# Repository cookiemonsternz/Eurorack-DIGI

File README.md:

# DIGI

_FPGA based programmable eurorack effects module_

#### What?
Yet another in my line of eurorack modules. This module is a prototyping platform for fpga based effects. It has a basic mono audio codec, two rotary encoders and 3 switches. It has two small led based displays in order to provide some feedback for the encoders. It consists of two user programmable leds with a diffuser.

DIGI utilises an ice40UP5K fpga chip, featuring 5280 luts and a 48Mhz clock. This is accompanied by a USB-SPI interface for easy programming. The board includes 64Mbits of PSRAM via single channel SPI and 256kbits of flash EEPROM. 

#### Why?
First and foremost: FPGAs are cool. Unfortunately, the world is quite starved of easy to use FPGA devboards, and especially so one which is designed for audio. This module acts as an easy to use prototyping environment for audio processing which would not be possible on MCUs.

This does kind of act as a counterpart to REV, but with an FPGA as to an MCU. This provides a bit more flexibility (and performance) and also provides a lot more memory to play with. 

#### How to use?
The board has a simple audio input and output, as well as two rotary encoders and switches, which are user programmable.

In terms of getting it set up, you'll need to program the fpga. To do this, follow the general setup guides for lattice radiant. It should be configured as a project for the iCE40UP5K-SG48I. An example showing the board acting as a basic buffer is available in the gateware folder.

Once assembled, the board uses a standard eurorack connector as well as standard 3.5mm audio jacks for input and output. Pretty plug and play :)

## Renders

## Schematics
Schematics are available as a [pdf](./hardware/digi/plots/digi.pdf) or as svgs in [hardware/digi/plots](./hardware/digi/plots/).

## Zine Page

## BOM
_Needed is how many I personally need :)_
| Part                            | Quantity | Needed | Source     | Link                                                                                                                                                           | Lot / Min Amount | Unit    | Net     | Running |
|---------------------------------|----------|--------|------------|----------------------------------------------------------------------------------------------------------------------------------------------------------------|------------------|---------|---------|---------|
| **Capacitors**                      |          |        |            |                                                                                                                                                                |                  |         |         |         |
| 20p Cap, 0402                   | 2        | 2      | JLCPCB     | https://jlcpcb.com/partdetail/1906-0402CG200J500NT/C1554                                                                                                       | 1                | $0.0021 | $0.0042 | $0.01   |
| 10n Cap, 0402                   | 4        | 4      | JLCPCB     | https://jlcpcb.com/partdetail/15869-CL05B103KB5NNNC/C15195                                                                                                     | 1                | $0.0025 | $0.0100 | $0.01   |
| 100n Cap, 0402                  | 25       | 25     | JLCPCB     | https://jlcpcb.com/partdetail/291005-CL05B104KB54PNC/C307331                                                                                                   | 1                | $0.0076 | $0.1900 | $0.20   |
| 1u Cap, 0402                    | 12       | 12     | JLCPCB     | https://jlcpcb.com/partdetail/53938-CL05A105KA5NQNC/C52923                                                                                                     | 1                | $0.0069 | $0.0828 | $0.28   |
| 4.7u Cap, 0402                  | 6        | 6      | JLCPCB     | https://jlcpcb.com/partdetail/24469-CL05A475MP5NRNC/C23733                                                                                                     | 1                | $0.0107 | $0.0642 | $0.35   |
| 10u Cap, 0402                   | 2        | 2      | JLCPCB     | https://jlcpcb.com/partdetail/16204-CL05A106MQ5NUNC/C15525                                                                                                     | 1                | $0.0186 | $0.0372 | $0.38   |
| 22u Cap, 0603                   | 1        | 1      | JLCPCB     | https://jlcpcb.com/partdetail/60514-CL10A226MQ8NRNC/C59461                                                                                                     | 1                | $0.0224 | $0.0224 | $0.41   |
| 10u Electrolytic Cap, P1.5xD4.0 | 2        | 0      | LCSC       | https://www.lcsc.com/product-detail/C503219.html                                                                                                               | 10               | $0.0143 | $0.0000 | $0.41   |
| 47u Electrolytic Cap, P2.5xD6.3 | 5        | 0      | LCSC       | https://www.lcsc.com/product-detail/C107641.html?spm=wm.fly.bg.7.xh___wm.fly.tp.1.ml&lcsc_vid=QAJaU1UHTldXXgADFFBaVFVfFFAMBl0CFVAIBQZQRVMxVlNeRlNcV1JXRFRaXjtW | 10               | $0.0665 | $0.0000 | $0.41   |
| 470u Electrolytic Cap, P5xD10.0 | 2        | 0      | LCSC       | https://www.lcsc.com/product-detail/C338196.html?spm=wm.fly.bg.3.xh___wm.fly.tp.1.ml&lcsc_vid=QAJaU1UHTldXXgADFFBaVFVfFFAMBl0CFVAIBQZQRVMxVlNeRlNcV1JXRFRaXjtW | 5                | $0.1883 | $0.0000 | $0.41   |
| **Resistors**                       |          |        |            |                                                                                                                                                                |                  |         |         |         |
| 0? Resistor, 0402               | 6        | 6      | JLCPCB     | https://jlcpcb.com/partdetail/17853-0402WGF0000TCE/C17168                                                                                                      | 1                | $0.001  | $0.0066 | $0.41   |
| 10? Resistor, 0402              | 1        | 1      | JLCPCB     | https://jlcpcb.com/partdetail/25820-0402WGF100JTCE/C25077                                                                                                      | 1                | $0.001  | $0.0009 | $0.41   |
| 100? Resistor, 0402             | 4        | 4      | JLCPCB     | https://jlcpcb.com/partdetail/25819-0402WGF1000TCE/C25076                                                                                                      | 1                | $0.0012 | $0.0048 | $0.42   |
| 470? Resistor, 0402             | 1        | 1      | JLCPCB     | https://jlcpcb.com/partdetail/25860-0402WGF4700TCE/C25117                                                                                                      | 1                | $0.0010 | $0.0010 | $0.42   |
| 1k? Resistor, 0402              | 2        | 2      | JLCPCB     | https://jlcpcb.com/partdetail/12256-0402WGF1001TCE/C11702                                                                                                      | 1                | $0.0011 | $0.0022 | $0.42   |
| 2.2k? Resistor, 0402            | 2        | 2      | JLCPCB     | https://jlcpcb.com/partdetail/26622-0402WGF2201TCE/C25879                                                                                                      | 1                | $0.0010 | $0.0020 | $0.42   |
| 10k? Resistor, 0805             | 8        | 8      | JLCPCB     | https://jlcpcb.com/partdetail/18102-0805W8F1002T5E/C17414                                                                                                      | 1                | $0.0034 | $0.0272 | $0.45   |
| 12k? Resistor, 0402             | 1        | 1      | JLCPCB     | https://jlcpcb.com/partdetail/26495-0402WGF1202TCE/C25752                                                                                                      | 1                | $0.0010 | $0.0010 | $0.45   |
| 39k? Resistor, 0402             | 1        | 1      | JLCPCB     | https://jlcpcb.com/partdetail/26526-0402WGF3902TCE/C25783                                                                                                      | 1                | $0.0011 | $0.0011 | $0.45   |
| 100k? Resistor, 0402            | 1        | 1      | JLCPCB     | https://jlcpcb.com/partdetail/26484-0402WGF1003TCE/C25741                                                                                                      | 1                | $0.0010 | $0.0010 | $0.45   |
| 1M? Resistor, 0402              | 1        | 1      | JLCPCB     | https://jlcpcb.com/partdetail/26826-0402WGF1004TCE/C26083                                                                                                      | 1                | $0.0011 | $0.0011 | $0.46   |
| **Diodes**                          |          |        |            |                                                                                                                                                                |                  |         |         |         |
| 1N4148WS, SOD-323               | 1        | 1      | JLCPCB     | https://jlcpcb.com/partdetail/2485-1N4148WS/C2128                                                                                                              | 1                | $0.0092 | $0.0092 | $0.46   |
| 1N5819WS, SOD-323               | 4        | 4      | JLCPCB     | https://jlcpcb.com/partdetail/GuangdongHottech-1N5819WS/C191023                                                                                                | 1                | $0.0111 | $0.0444 | $0.51   |
| **Other Components**                |          |        |            |                                                                                                                                                                |                  |         |         |         |
| TL072CDT                        | 1        | 1      | JLCPCB     | https://jlcpcb.com/partdetail/STMicroelectronics-TL072CDT/C6961                                                                                                | 1                | $0.1570 | $0.1570 | $0.67   |
| EC11 Rotary Encoder SW          | 2        | 0      | Aliexpress | https://www.aliexpress.com/item/1005010400760178.html                                                                                                          | 5                | $0.8580 | $0.0000 | $0.67   |
| SPDT Switch                     | 3        | 3      | Aliexpress | https://www.aliexpress.com/item/1005005370002265.html                                                                                                          | 5                | $0.8520 | $4.2600 | $4.93   |
| PJ301M-12 Audio Jack            | 2        | 0      | Aliexpress | https://www.aliexpress.com/item/1005004864182675.html                                                                                                          | 10               | $0.4440 | $0.0000 | $4.93   |
| 2x08 IDC Connector              | 1        | 0      | LCSC       | https://www.lcsc.com/product-detail/C7430313.html                                                                                                              | 5                | $0.0993 | $0.0000 | $4.93   |
| X322512MSB4SI 12MHz Crystal     | 1        | 1      | JLCPCB     | https://jlcpcb.com/partdetail/YXC_CrystalOscillators-X322512MSB4SI/C9002                                                                                       | 1                | $0.0740 | $0.0740 | $5.00   |
| USB B Micro Port                | 1        | 1      | JLCPCB     | https://jlcpcb.com/partdetail/SHOUHAN-MicroXNJ/C404969                                                                                                         | 1                | $0.0406 | $0.0406 | $5.04   |
| 256kB EEPROM, AT24C256C-SSHL-T  | 1        | 1      | JLCPCB     | https://jlcpcb.com/partdetail/MicrochipTech-AT24C256C_SSHLT/C6482                                                                                              | 1                | $0.3886 | $0.3886 | $5.43   |
| 64Mbit PSRAM, APS6404L-SQN-SN   | 1        | 1      | JLCPCB     | https://jlcpcb.com/partdetail/APMemory-APS6404L_SQNSN/C5360304                                                                                                 | 1                | $2.4684 | $2.4684 | $7.90   |
| Neopixel tht, 5mm               | 8        | 8      | Aliexpress | https://www.aliexpress.com/item/1005006447915276.html                                                                                                          | 20               | $0.2595 | $5.1900 | $13.09  |
| Audio Codec, ES8311             | 1        | 1      | JLCPCB     | https://jlcpcb.com/partdetail/1044199-ES8311/C962342                                                                                                           | 1                | $0.5514 | $0.5514 | $13.64  |
| Reset Button                    | 1        | 1      | JLCPCB     | https://jlcpcb.com/partdetail/XUNPU-TS_1088AR02016/C720477                                                                                                     | 1                | $0.0551 | $0.0551 | $13.69  |
| Ferrite Bead, 600R              | 2        | 2      | JLCPCB     | https://jlcpcb.com/partdetail/Sunlord-GZ2012D601TF/C1017                                                                                                       | 1                | $0.0323 | $0.0646 | $13.76  |
| 22uH Inductor, 0805             | 2        | 2      | JLCPCB     | https://jlcpcb.com/partdetail/Sunlord-SDFL2012T220KTF/C32375                                                                                                   | 1                | $0.0689 | $0.1378 | $13.90  |
| LED Yellow                      | 1        | 1      | JLCPCB     | https://jlcpcb.com/partdetail/Hubei_KENTOElec-KT0805Y/C2296                                                                                                    | 1                | $0.0152 | $0.0152 | $13.91  |
| LED Green                       | 1        | 1      | JLCPCB     | https://jlcpcb.com/partdetail/Hubei_KENTOElec-KT0805G/C2297                                                                                                    | 1                | $0.0162 | $0.0162 | $13.93  |
| LED Red                         | 1        | 1      | JLCPCB     | https://jlcpcb.com/partdetail/85425-NCD0805R1/C84256                                                                                                           | 1                | $0.0133 | $0.0133 | $13.94  |
| AMS1117-3.3                     | 1        | 1      | JLCPCB     | https://jlcpcb.com/partdetail/Advanced_MonolithicSystems-AMS1117_33/C6186                                                                                      | 1                | $0.1971 | $0.1971 | $14.14  |
| XL1509-ADJ                      | 2        | 2      | JLCPCB     | https://jlcpcb.com/partdetail/XLSEMI-XL1509ADJE1/C74192                                                                                                        | 1                | $0.2717 | $0.5434 | $14.68  |
| **Other**                           |          |        |            |                                                                                                                                                                |                  |         |         |         |
| PCB                             | 1        | 1      | JLCPCB     | NA                                                                                                                                                             | 5                | $1.6600 | $8.3000 | $22.98  |
| Aluminium Plate (100x200x2mm)   | 1        | 1      | Aliexpress | https://www.aliexpress.com/item/1005007160296738.html                                                                                                          | 1                | $6.2300 | $6.2300 | $29.21  |
| **Total**                           |          |        |            |                                                                                                                                                                |                  |         |         | $29.21  |

| **Totals**                          | **Money**  |
|---------------------------------|--------|
| Aliexpress, Inc. Shipping + Tax | $24.57 |
| JLCPCB, Inc. Shipping + Tax     | $38.84 |
| Total                           | $63.41 |

## CAD Links
Heres the links to the CAD source, Onshape:
[Panel source](https://cad.onshape.com/documents/423b155ae421053f9c0db9a4/w/13826012c5a1515169c92444/e/776c4f51f2d171959c208a60?renderMode=0&uiState=6a7d7e6ffb2cc2f8f4025e10)

## Directory Structure
- **hardware/**
    - **bom/** - BOM Files (CSV and LibreOffice Calc)
    - **cad/** - CAD Files
        - **render/** - Files for rendering (inc. gltf models)
    - **digi/** - KiCad files
        - **lib/** - External libraries
        - **production/** - Production files (Gerber, etc.)
        - **plots/** - Schematic plot
- **journals/**
- **zine/** - Zine page

#### This project was created for [Hack Club](https://hackclub.com/) - [Fallout](https://fallout.hackclub.com/)

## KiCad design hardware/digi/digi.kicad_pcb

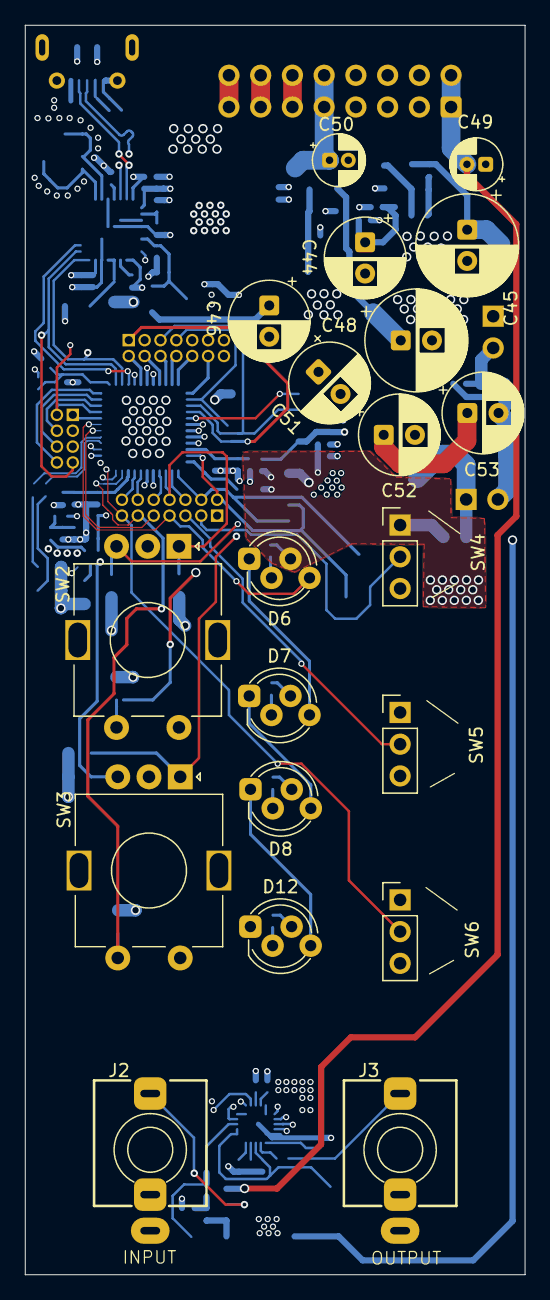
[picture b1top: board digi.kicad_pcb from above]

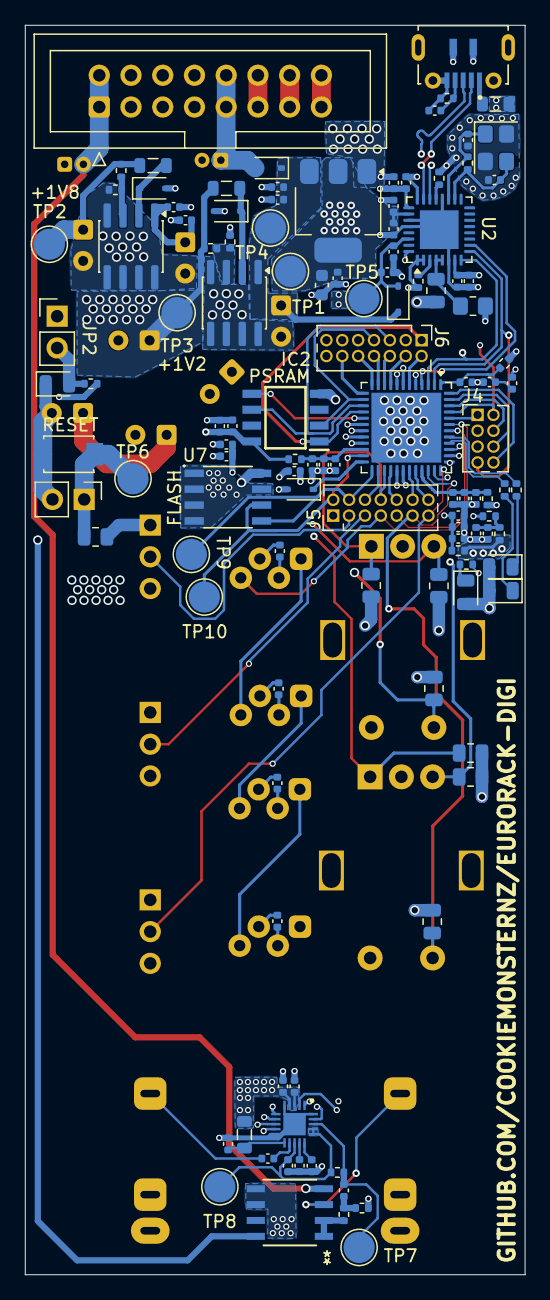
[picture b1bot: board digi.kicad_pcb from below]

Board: 6 copper layers, 40.0 x 100.0 mm, 139 parts (119 on the bottom side), 86 nets.

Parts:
C1, C4, C6, C8, C11, C14, C19, C21, C23, C25, C30, C31, C34, C36, C37, C38, C39, C42, C54, C55, C60: 100n; C_0402_1005Metric
C2, C40: 10u; C_0402_1005Metric
C3, C7, C10, C13, C26, C27, C28, C29, C32, C33, C43, C47: 1u; C_0402_1005Metric
C5, C9, C12, C15: 10n; C_0402_1005Metric
C16, C17: 20p; C_0402_1005Metric
C18, C20, C22, C24, C35, C61: 4.7u; C_0402_1005Metric
C41: 22u; C_0603_1608Metric
C44, C46, C51, C52, C53: 47u; CP_Radial_D6.3mm_P2.50mm
C45, C48: 470u; CP_Radial_D8.0mm_P2.50mm
C49, C50: 10u; CP_Radial_D4.0mm_P1.50mm
D1: 1N4148; D_SOD-323
D2: LED; LED_0805_2012Metric
D3, D4, D5, D17: 1N5819; D_SOD-323
D6, D7, D8, D12: NeoPixel_THT; LED_D5.0mm-4_RGB_Staggered_Pins
D9: LED_R; LED_0805_2012Metric
D10: LED_G; LED_0805_2012Metric
D11: LED_B; LED_0805_2012Metric
IC1: ES8311; QFN40P300X300X60-21N
IC2: APS6404L-SQN-SN; SOIC127P600X175-8N
J1: USB_B_Micro; SHOUHAN_MICROXNJ
J2: IN; Jack_3.5mm_QingPu_WQP-PJ301M-12_Vertical
J3: OUT; Jack_3.5mm_QingPu_WQP-PJ301M-12_Vertical
J4: Bank 2; PinHeader_2x04_P1.27mm_Vertical
J5: Bank 0; PinHeader_2x07_P1.27mm_Vertical
J6: Bank 1; PinHeader_2x07_P1.27mm_Vertical
J10: Conn_02x08_Odd_Even; IDC-Header_2x08_P2.54mm_Vertical
JP1: RESET_J; PinHeader_1x02_P2.54mm_Vertical
JP2: DONE_J; PinHeader_1x02_P2.54mm_Vertical
L1: 600R/1A; L_0805_2012Metric
L2: 180r-100M; L_0805_2012Metric
L3, L4: 47uH; L_0805_2012Metric
R1, R28, R29, R30: 100; R_0402_1005Metric
R2, R3, R4, R5, R6, R23: 0; R_0402_1005Metric
R7, R15, R16, R17, R18, R19, R20, R21: 10k; R_0805_2012Metric
R8, R22: 2.2k; R_0402_1005Metric
R9, R13: 1M; R_0402_1005Metric
R10: 12k; R_0402_1005Metric
R11: 100k; R_0402_1005Metric
R12: 39k; R_0402_1005Metric
R14: DNP; R_0805_2012Metric_Pad1.20x1.40mm_HandSolder
R24: 470; R_0402_1005Metric
R25, R26: 1k; R_0402_1005Metric
R27: 10; R_0402_1005Metric
SW1: RESET_SW; SW_TS-1088-AR02016
SW2: Encoder1; RotaryEncoder_Alps_EC11E-Switch_Vertical_H20mm_MountingHoles
SW3: Encoder2; RotaryEncoder_Alps_EC11E-Switch_Vertical_H20mm_MountingHoles
SW4, SW5, SW6: SW_SPDT; PinHeader_1x03_P2.54mm_Vertical
TP1: 3V3; TestPoint_Pad_D2.5mm
TP2: 1V8; TestPoint_Pad_D2.5mm
TP3: 1V2; TestPoint_Pad_D2.5mm
TP4: VDD; TestPoint_Pad_D2.5mm
TP5: VBUS; TestPoint_Pad_D2.5mm
TP6: RESET; TestPoint_Pad_D2.5mm
TP7: AUDIO_IN; TestPoint_Pad_D2.5mm
TP8: AUDIO_VMID; TestPoint_Pad_D2.5mm
TP9: FLASH_SDA; TestPoint_Pad_D2.5mm
TP10: FLASH_CLK; TestPoint_Pad_D2.5mm
U1: ICE40UP5K-SG48ITR; QFN-48-1EP_7x7mm_P0.5mm_EP5.6x5.6mm
U2: FT4222HQ; VQFN-32-1EP_5x5mm_P0.5mm_EP3.1x3.1mm
U3: TL072; D8_TEX_STM
U4: AMS1117-3.3; SOT-223-3_TabPin2
U5, U6: XL1509-ADJ; SOIC-8_3.9x4.9mm_P1.27mm
U7: AT24C256C-SSHL-T; SOIC127P600X175-8N
Y1: 12MHz - X322512MSB4SI; Crystal_SMD_3225-4Pin_3.2x2.5mm

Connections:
+1V2: C48.1, L4.2, R2.1, R3.1, R27.2, TP3.1 (1_1)
+1V8: C34.1, C35.1, C45.1, IC2.8 (VDD), L3.2, R5.1, R24.2, TP2.1 (1_1)
+3V3: C6.1, C20.1, C21.1, C22.1, C23.1, C24.1, C25.1, C30.1, C31.1, C37.1, C38.1, C41.1, C42.1, C54.1, C55.1, C60.1, C61.1, D1.2 (A), D6.3 (VDD), D7.3 (VDD), D8.3 (VDD), D9.2 (A), D10.2 (A), D11.2 (A), D12.3 (VDD), IC1.3 (PVDD), IC1.4 (DVDD), L2.1, R4.1, R6.1, R7.1, R8.1, R15.1, R16.1, R17.1, R18.1, R19.1, R20.1, R21.2, R22.2, SW4.1 (A), SW5.1 (A), SW6.1 (A), TP1.1 (1_1), U2.1 (DEBUGGER), U2.2 (~STEST_RST), U2.7 (VCCIO), U2.25 (VOUT3V3), U2.26 (VCCIN), U4.2 (VO), U7.8 (VCC)
+12V: C50.1, D17.2 (A), J10.9, J10.10, U3.8 (V+)
-12V: C49.2, J10.1, J10.2, U3.4 (V-)
/SPI_VCCIO1: C10.1, C11.1, C12.1, R5.2, U1.22 (SPI_VCCIO1)
/USB_D+: J1.3 (D+), U2.22 (DM)
/USB_D-: J1.2 (D-), U2.23 (DP)
/VCCIO_0: C13.1, C14.1, C15.1, R6.2, U1.33 (VCCIO_0)
/VCCIO_2: C7.1, C8.1, C9.1, R4.2, U1.1 (VCCIO_2)
AUDIO_VMID: C26.1, IC1.13 (OUTN), IC1.16 (VMID), IC1.17 (MIC1N), R13.2, TP8.1 (1_1)
AVDD: C29.1, IC1.11 (AVDD), L2.2
CDONE: JP2.1 (A), U1.7 (CDONE)
CRESET: JP1.1 (A), R7.2, SW1.1, TP6.1 (1_1), U1.8 (~CRESET)
ENCODER_1_A: J5.8, R17.2, SW2.A, U1.27 (IOT_38b)
ENCODER_1_B: J5.6, R18.2, SW2.B, U1.26 (IOT_39a)
ENCODER_1_SW: J5.14, R15.2, SW2.S1, U1.32 (IOT_43a)
ENCODER_2_A: J5.10, R19.2, SW3.A, U1.28 (IOT_41a)
ENCODER_2_B: J5.12, R20.2, SW3.B, U1.31 (IOT_42b)
ENCODER_2_SW: J5.11, R16.2, SW3.S1, U1.34 (IOT_44b)
GND: C1.2, C2.2, C3.2, C4.2, C5.2, C6.2, C7.2, C8.2, C9.2, C10.2, C11.2, C12.2, C13.2, C14.2, C15.2, C16.2, C17.2, C18.2, C19.2, C20.2, C21.2, C22.2, C23.2, C24.2, C25.2, C26.2, C27.2, C28.2, C29.2, C30.2, C31.2, C34.2, C35.2, C36.2, C37.2, C38.2, C39.2, C40.2, C41.2, C42.2, C43.2, C44.2, C45.2, C46.2, C47.2, C48.2, C49.1, C50.2, C51.2, C52.2, C53.2, C54.2, C55.2, C60.2, C61.2, D2.1 (K), D4.2 (A), D5.2 (A), D6.2 (GND), D7.2 (GND), D8.2 (GND), D12.2 (GND), IC1.5 (DGND), IC1.10 (AGND), IC1.20 (CE), IC1.21 (EP), IC2.4 (VSS), J1.5 (GND), J1.SH (Shield), J2.S, J2.TN, J3.S, J3.TN, J10.3, J10.4, J10.5, J10.6, J10.7, J10.8, JP1.2 (B), R10.2, R12.1, R14.1, R23.2, R25.1, R26.1, SW1.2, SW2.C, SW2.S2, SW3.C, SW3.S2, SW4.3 (C), SW5.3 (C), SW6.3 (C), U1.49 (GND), U2.6 (DGND), U2.20 (UGND), U2.24 (UGND), U2.27 (AGND), U2.28 (DGND), U2.33 (EP), U3.5 (+), U3.6 (-), U4.1 (GND), U5.4 (~EN), U5.5 (GND), U5.6 (GND), U5.7 (GND), U5.8 (GND), U6.4 (~EN), U6.5 (GND), U6.6 (GND), U6.7 (GND), U6.8 (GND), U7.1 (A0), U7.2 (A1), U7.3 (A2), U7.4 (GND), U7.7 (WP), Y1.2 (G), Y1.4 (G)
ICE_I2C_CLK: IC1.1 (CCLK), J5.2, TP10.1 (1_1), U1.23 (IOT_37a), U7.6 (SCL)
ICE_I2C_SDA: IC1.19 (CDATA), J5.4, TP9.1 (1_1), U1.25 (IOT_36b), U7.5 (SDA)
ICE_I2S_BCLK: IC1.6 (SCLK/DMIC_SCL), J4.6, U1.47 (IOB_2a)
ICE_I2S_DIN: IC1.9 (DSDIN), J4.8, U1.48 (IOB_4a)
ICE_I2S_DOUT: IC1.7 (ASDOUT), J4.1, U1.44 (IOB_3b_G6)
ICE_I2S_MCLK: IC1.2 (MCLK), J4.4, U1.46 (IOB_0a)
ICE_I2S_WS: IC1.8 (LRCK), J5.1, U1.38 (IOT_50b)
ICE_LED_0: R30.1, U1.39 (RGB0)
ICE_LED_1: R29.1, U1.40 (RGB1)
ICE_LED_2: R28.1, U1.41 (RGB2)
ICE_SPI0_MISO: IC2.2 (SO/SIO[1]), J6.7, U1.14 (IOB_32a_SPI_SO)
ICE_SPI0_MOSI: IC2.5 (SI/SIO[0]), J6.3, U1.17 (IOB_33b_SPI_SI)
ICE_SPI0_SCK: IC2.6 (SCLK), J6.5, U1.15 (IOB_34a_SPI_SCK)
ICE_SPI1_MISO: J4.7, U1.2 (IOB_6a), U2.9 (MISO)
ICE_SPI1_MOSI: J4.5, U1.4 (IOB_8a), U2.10 (MOSI)
ICE_SPI1_SCK: J4.3, U1.3 (IOB_9b), U2.8 (SCK)
IOB_13b: J6.2, U1.6 (IOB_13b)
IOB_16a: J6.4, U1.9 (IOB_16a)
IOB_18a: J6.6, U1.10 (IOB_18a)
IOB_20a: J6.8, U1.11 (IOB_20a)
IOB_22a: J6.10, U1.12 (IOB_22a)
IOB_23b: J6.9, U1.21 (IOB_23b)
IOB_24a: J6.12, U1.13 (IOB_24a)
IOB_25b_G3: J6.11, U1.20 (IOB_25b_G3)
IOB_29b: J6.13, U1.19 (IOB_29b)
IOB_31b: J6.14, U1.18 (IOB_31b)
IOT_51a: J5.9, U1.42 (IOT_51a)
NEOPIXEL_DIN: D6.4 (DIN), J5.7, U1.43 (IOT_49a)
unnamed: C1.1, C2.1, R1.1, R2.2
unnamed: C32.1, R11.2, R12.2
unnamed: C33.1, J3.T
unnamed: D2.2 (A), JP2.2 (B), R8.2
unnamed: D4.1 (K), L3.1, U5.2 (OUT)
unnamed: D5.1 (K), L4.1, U6.2 (OUT)
unnamed: D6.1 (DOUT), D7.4 (DIN)
unnamed: D7.1 (DOUT), D8.4 (DIN)
unnamed: D9.1 (K), R28.2
unnamed: D10.1 (K), R29.2
unnamed: D11.1 (K), R30.2
unnamed: D8.1 (DOUT), D12.4 (DIN)
unnamed: C28.1, IC1.15 (ADCVREF)
unnamed: C27.1, IC1.14 (DACVREF)
unnamed: C32.2, IC1.18 (MIC1P/DMIC_SDA), R13.1, TP7.1 (1_1)
unnamed: C33.2, IC1.12 (OUTP)
unnamed: C36.1, J1.4 (ID), R23.1
unnamed: J1.1 (VBUS), L1.2
unnamed: R14.2, R21.1, U2.4 (DCNF0), U2.5 (DCNF1)
unnamed: R10.1, U2.21 (RREF)
unnamed: R22.1, U2.3 (~RESET)
unnamed: J2.T, U3.3 (+)
unnamed: R11.1, U3.1, U3.2 (-)
unnamed: R24.1, R25.2, U5.3 (FB)
unnamed: R26.2, R27.1, U6.3 (FB)
PSRAM_SPI0_CS: IC2.1 (~CE), J6.1, U1.16 (IOB_35b_SPI_SS)
SW_1: J5.3, SW4.2 (B), U1.37 (IOT_45a_G1)
SW_2: J5.5, SW5.2 (B), U1.35 (IOT_46b_G0)
SW_3: J5.13, SW6.2 (B), U1.36 (IOT_48b)
USB_SPI1_CS: J4.2, U1.45 (IOB_5b), U2.32 (~SS)
USB_XSCI: C16.1, R9.2, U2.18 (XSCI), Y1.3
USB_XSCO: C17.1, R9.1, U2.19 (XSCO), Y1.1
VBUS: C18.1, C19.1, D3.2 (A), L1.1, TP5.1 (1_1), U2.30 (VBUS_DET)
VCC: C3.1, C4.1, C5.1, R3.2, U1.5 (VCC), U1.30 (VCC)
VCCPLL: R1.2, U1.29 (VCCPLL)
VDD: C39.1, C40.1, C43.1, C44.1, C46.1, C47.1, C51.1, C52.1, C53.1, D3.1 (K), D17.1 (K), TP4.1 (1_1), U4.3 (VI), U5.1 (VIN), U6.1 (VIN)
VPP_2V5: D1.1 (K), U1.24 (VPP_2V5)

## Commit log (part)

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2026-06-08 start schematic
